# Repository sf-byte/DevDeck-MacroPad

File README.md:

# DevDeck-MacroPad
The DevDeck is a smallish MacroPad designed to make programming more efficient.
It has 5 switches, two LED status lights, an OLED screen to display some info, and uses circuitpython with some libraries as the firmware.
---
# Features

* 5 Switches for doing macros,
* 128x32 Oled display,
* 2 SK6812 Mini E LED lights,
* Custom firmware including a host.py for further customization post building.
---
# CAD

Made in Fusion360 with blood, sweat, tears, and hours of revisions.

---
# PCB

Made in Kicad 9.0

### Schematic

I used an SK6812 on the schematic as a stand in for the OLED, as I didn't have a symbol for it.

### PCB

---
# Firmware

As this is my first time ever designing/building hardware, and have never made firmware for anything in my life, I used ChatGPT as a help (all the ideas for what does what and how stuff work (so the basic logic) came from me).

The firmware has by default 4 layers for the macro keys:
1. Edit
	1. Cut
	2. Copy
	3. Paste
	4. Undo
	5. Redo
2. Git control
	1. `git add .`
	2. `git commit -m ""`
	3. `git push origin main`
	4. `git pull`
	5. `git init`
3. Code snippets
	1. ```python
    	try:
			...
		except:
			...
	2. ```python
    	while True:
			...
	3. ```python
    	def main():
			...
	4. ```python
    	if ...:
			...
		elif ...:
			...
		else:
			...
	5. ```python
    	from time import sleep as delay
		while True:
			try:
				main()
			except KeyboardInterrupt:
				print("\nGoodbye", end="", flush=True)
				delay(0.5)
				print(".", end="", flush=True)
				delay(0.5)
				print(".", end="", flush=True)
				delay(0.5)
				print(".", end="", flush=True)
				delay(0.5)
				exit(0)
4. Window control
	1. win + up arrow
	2. win + left arrow
	3. win + d
	4. win + right arrow
	5. win + down arrow

To switch between macro layers you hit the middle(3) and either the left(2) or right(4) switches to go back and forward in the macro layers, respectively.  

The screen by default just shows what macro layer you're currently on.  
(if you add layers to the screen it still shows the current macro layer name on the top, plus the two lines of text you added (currently only supports text).
To switch between screen layers you hit the middle(3) and either the top(1) or bottom(5) switches to back and forward in the screen layers, repectively.)

The LED status lights show the following:  
1. The right one:
	* white when no macro is being triggered
	* green when a macro is being triggered
	* red when there's a macro error

2. The left one:
	* white when no layer is being changed
	* green when a macro layer is being changed
	* blue when a screen layer is being changed
	* red when there's a layer changing error

### Host.py

I added functionality to change or even add layers to the macropad from the comfort of your own computer, even post build and install, using the host.py file.
You can add and change both the macro layers, and the screen layers.
I tried to make it as user-friendly as possible, so whoever is using it can do so with ease.
---
# BOM

* 1 3D printed case
* 1 PCB
* 1 Seeed XIAO RP2040
* 5 Cherry MX switches
* 5 DSA keycaps
* 2 SK6812 Mini E LED lights
* 1 0.91" 128x32 OLED display
* 4 M3 Heatset inserts
* 4 M3x16 SCHS bolts

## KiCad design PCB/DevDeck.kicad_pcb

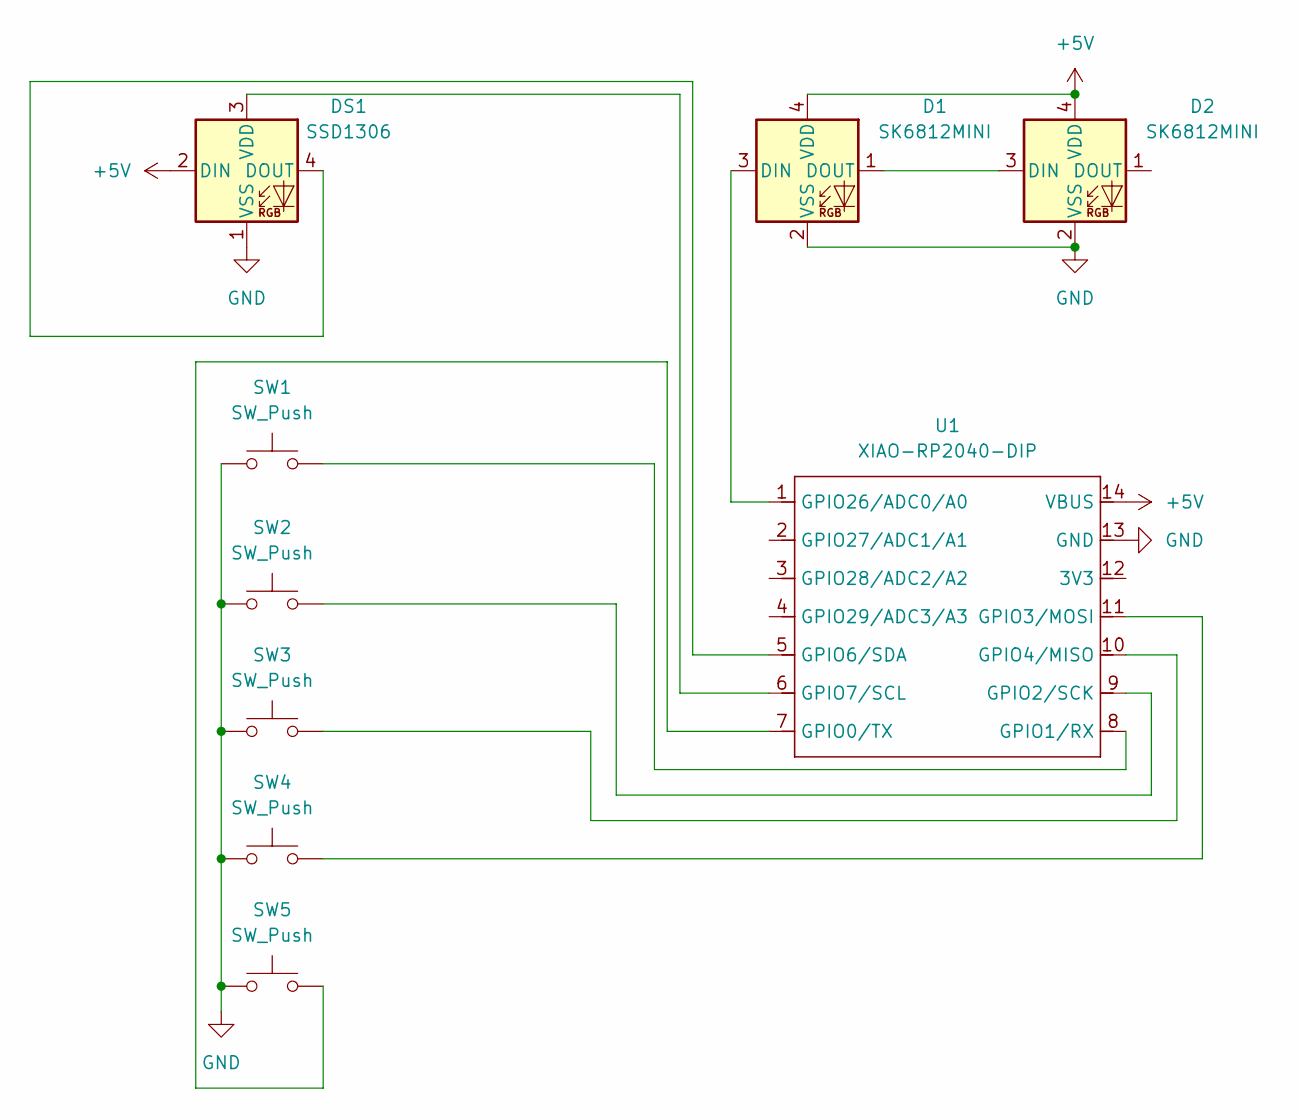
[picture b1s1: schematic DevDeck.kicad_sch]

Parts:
D1, D2: SK6812MINI; LED_SK6812MINI_PLCC4_3.5x3.5mm_P1.75mm
DS1: SSD1306; SSD1306-0.91-OLED-4pin-128x32
SW1, SW2, SW3, SW4, SW5: SW_Push; SW_Cherry_MX_1.00u_PCB
U1: XIAO-RP2040-DIP

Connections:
+5V: D1.4 (VDD), D2.4 (VDD), DS1.2 (DIN), U1.14 (VBUS)
GND: D1.2 (VSS), D2.2 (VSS), DS1.1 (VSS), SW1.1, SW2.1, SW3.1, SW4.1, SW5.1, U1.13 (GND)
unnamed: D1.3 (DIN), U1.1 (GPIO26/ADC0/A0)
unnamed: D1.1 (DOUT), D2.3 (DIN)
unnamed: DS1.4 (DOUT), U1.5 (GPIO6/SDA)
unnamed: DS1.3 (VDD), U1.6 (GPIO7/SCL)
unnamed: SW5.2, U1.7 (GPIO0/TX)
unnamed: SW1.2, U1.8 (GPIO1/RX)
unnamed: SW2.2, U1.9 (GPIO2/SCK)
unnamed: SW4.2, U1.11 (GPIO3/MOSI)
unnamed: SW3.2, U1.10 (GPIO4/MISO)

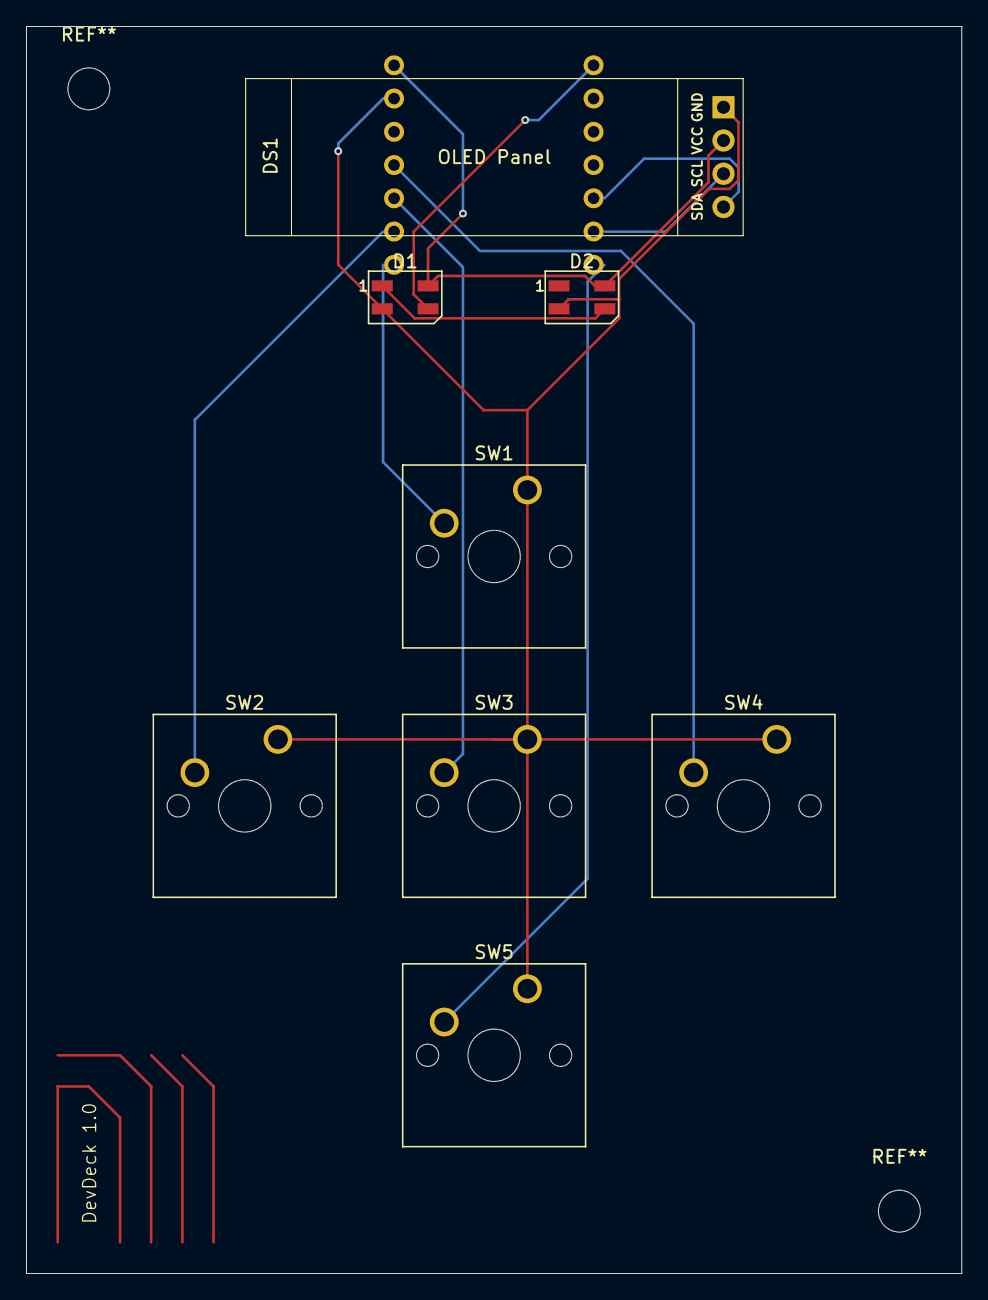
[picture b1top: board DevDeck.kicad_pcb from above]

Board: 2 copper layers, 71.4 x 95.2 mm, 9 parts (1 on the bottom side), 11 nets.

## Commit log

2025-12-09 Fix typo in README firmware description
    Corrected a typo in the firmware section.
2025-12-09 Clarify schematic component usage in README
    Added note about using SK6812 as a placeholder for OLED.
2025-12-10 Fix typo in README.md
2025-12-10 Improve formatting of code snippets in README
    Updated code snippets in README.md for better readability.
2025-12-10 Fix formatting issues in README.md
2025-12-10 Refactor Python code examples in README
    Updated Python code snippets in README for clarity.
2025-12-10 Refactor README.md for better structure and clarity
    Updated the README to improve formatting and organization of sections.
2025-12-10 Fix grammar and wording in README.md
    Corrected capitalization and improved wording in the README.
2025-12-10 Update README with macro and screen layer instructions
    Clarified instructions on switching between macro and screen layers in the README.
2025-12-10 Fix typos and enhance README instructions
    Corrected typos and improved clarity in README.
2025-12-10 Update README with LED status
    Added LED status light descriptions
2025-12-10 Fix formatting and numbering in README.md
2025-12-10 Fix indentation in Python code snippets in README
2025-12-10 Improve README.md description for host.py
    Enhanced the description of the host.py functionality for clarity and user-friendliness.
2025-12-17 Fix typo in README about macro layers
    Corrected a typo in the README regarding macro layers.
2025-12-21 pin naming correction and dependency resolving
